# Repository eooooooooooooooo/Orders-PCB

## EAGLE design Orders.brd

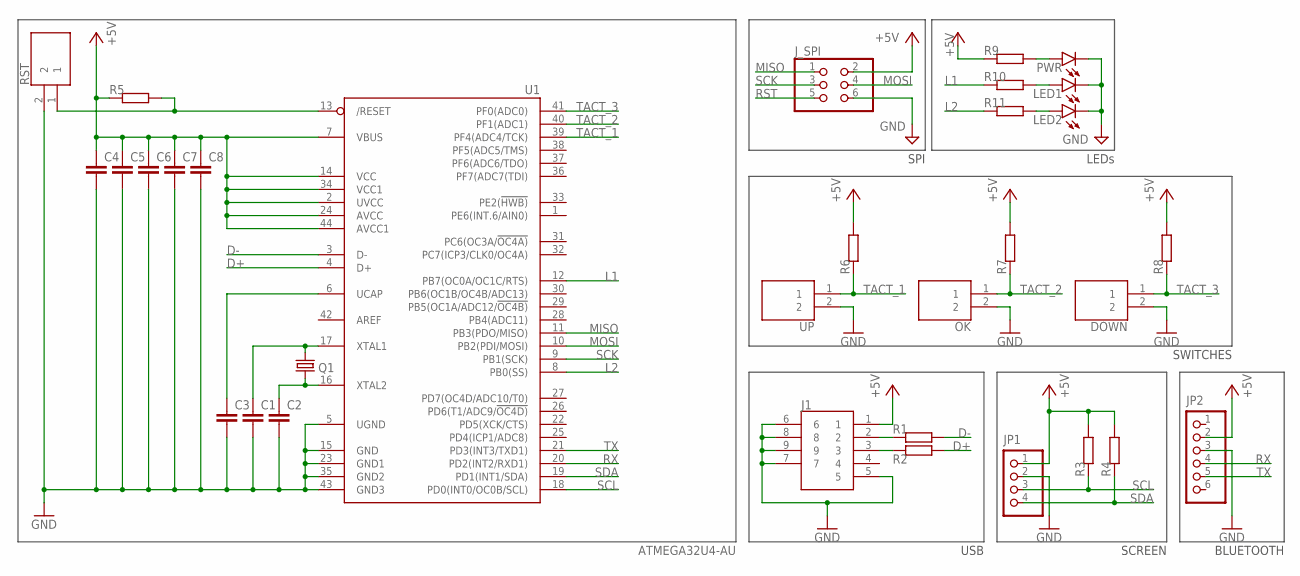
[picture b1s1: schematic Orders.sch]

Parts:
C1, C2, C3, C4, C5, C6, C7, C8: C-EUC1206; C1206
DOWN: KSR231GLFS; KSR
J1: 10104111-0001LF; 101041110001LF
JP1: PINHD-1X4; 1X04
JP2: PINHD-1X6; 1X06
J_SPI: PINHD-2X3; 2X03
LED1, LED2: LED3MM
OK: KSR231GLFS; KSR
PWR: LED3MM
Q1: CRYSTALHC49UP; HC49UP
R1, R2, R3, R4, R5, R6, R7, R8, R9, R10, R11: R-EU_R1206; R1206
RST: KSR231GLFS; KSR
U1: ATMEGA32U4-AU; TQFP44
UP: KSR231GLFS; KSR

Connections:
+5V: C4.1, C5.1, C6.1, C7.1, C8.1, J1.1, JP1.1, JP2.2, J_SPI.2, R3.2, R4.2, R5.1, R6.2, R7.2, R8.2, R9.2, U1.2 (UVCC), U1.7 (VBUS), U1.14 (VCC), U1.24 (AVCC), U1.34 (VCC1), U1.44 (AVCC1)
D+: R2.2, U1.4 (D+)
D-: R1.2, U1.3 (D-)
GND: C1.2, C2.2, C3.2, C4.2, C5.2, C6.2, C7.2, C8.2, DOWN.2, J1.5, J1.6, J1.7, J1.8, J1.9, JP1.2, JP2.3, J_SPI.6, LED1.K (C), LED2.K (C), OK.2, PWR.K (C), RST.2, U1.5 (UGND), U1.15 (GND), U1.23 (GND1), U1.35 (GND2), U1.43 (GND3), UP.2
L1: R10.2, U1.12 (PB7(OC0A/OC1C/RTS))
L2: R11.2, U1.8 (PB0(SS))
MISO: J_SPI.1, U1.11 (PB3(PDO/MISO))
MOSI: J_SPI.4, U1.10 (PB2(PDI/MOSI))
unnamed: J1.2, R1.1
unnamed: J1.3, R2.1
unnamed: C1.1, Q1.2, U1.17 (XTAL1)
unnamed: C2.1, Q1.1, U1.16 (XTAL2)
unnamed: PWR.A, R9.1
unnamed: LED1.A, R10.1
unnamed: LED2.A, R11.1
RST: J_SPI.5, R5.2, RST.1, U1.13 (/RESET)
RX: JP2.4, U1.20 (PD2(INT2/RXD1))
SCK: J_SPI.3, U1.9 (PB1(SCK))
SCL: JP1.3, R3.1, U1.18 (PD0(INT0/OC0B/SCL))
SDA: JP1.4, R4.1, U1.19 (PD1(INT1/SDA))
TACT_1: R6.1, U1.39 (PF4(ADC4/TCK)), UP.1
TACT_2: OK.1, R7.1, U1.40 (PF1(ADC1))
TACT_3: DOWN.1, R8.1, U1.41 (PF0(ADC0))
TX: JP2.5, U1.21 (PD3(INT3/TXD1))
UCAP: C3.1, U1.6 (UCAP)

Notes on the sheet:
USB
SCREEN
BLUETOOTH
SPI
SWITCHES
LEDs

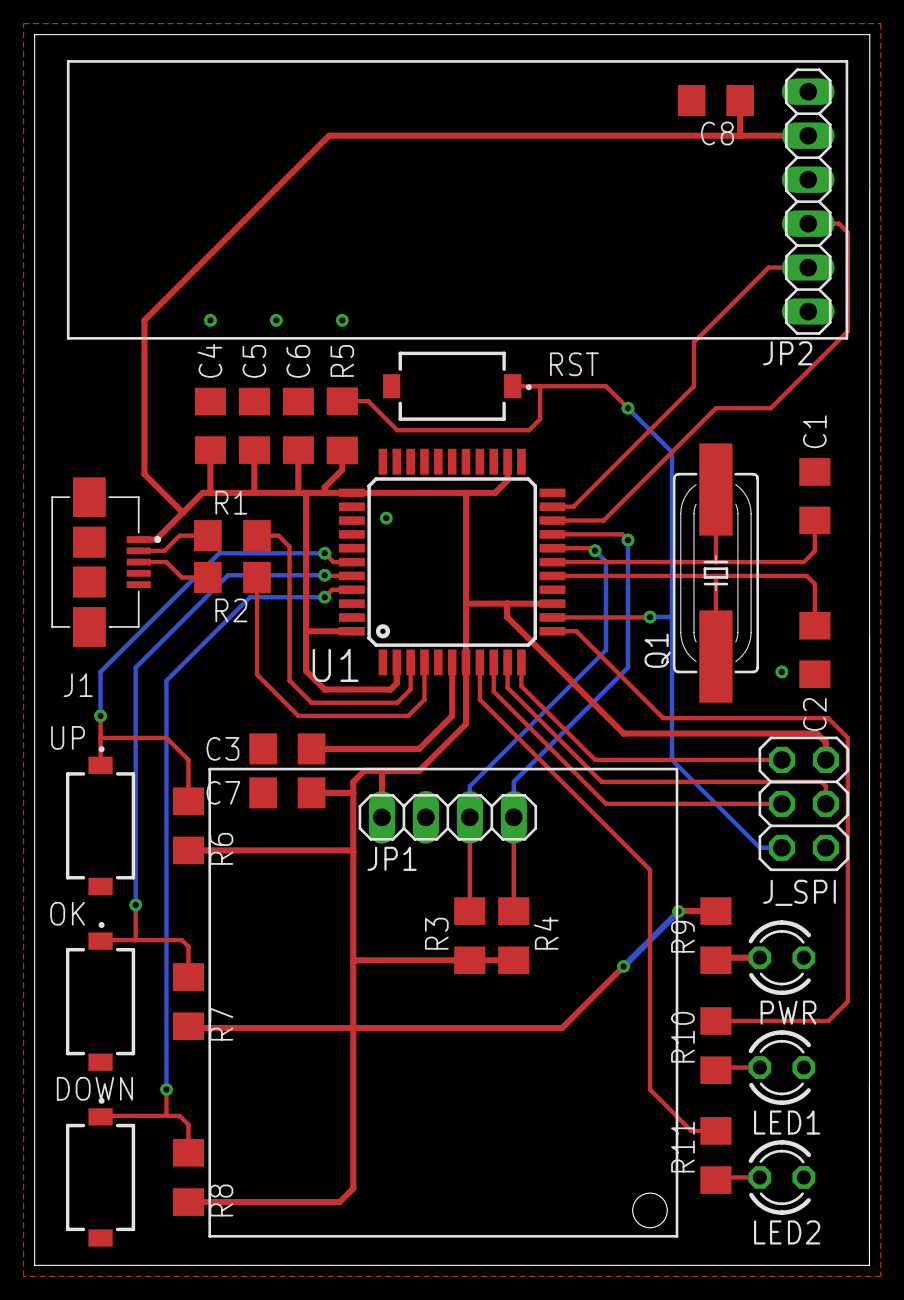
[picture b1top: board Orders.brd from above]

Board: 2 copper layers, 48.3 x 71.1 mm, 32 parts (0 on the bottom side), 25 nets.

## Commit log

2020-01-03 Init commit
2020-01-03 Created schematic file
2020-01-03 Create LICENSE
2020-01-04 Began BoM
2020-01-04 Added I2C pull-up resistances
2020-01-04 Added passives for uC
2020-01-04 Finished schematic
2020-01-05 Refined ground planes
2020-01-18 Final commit, added software
